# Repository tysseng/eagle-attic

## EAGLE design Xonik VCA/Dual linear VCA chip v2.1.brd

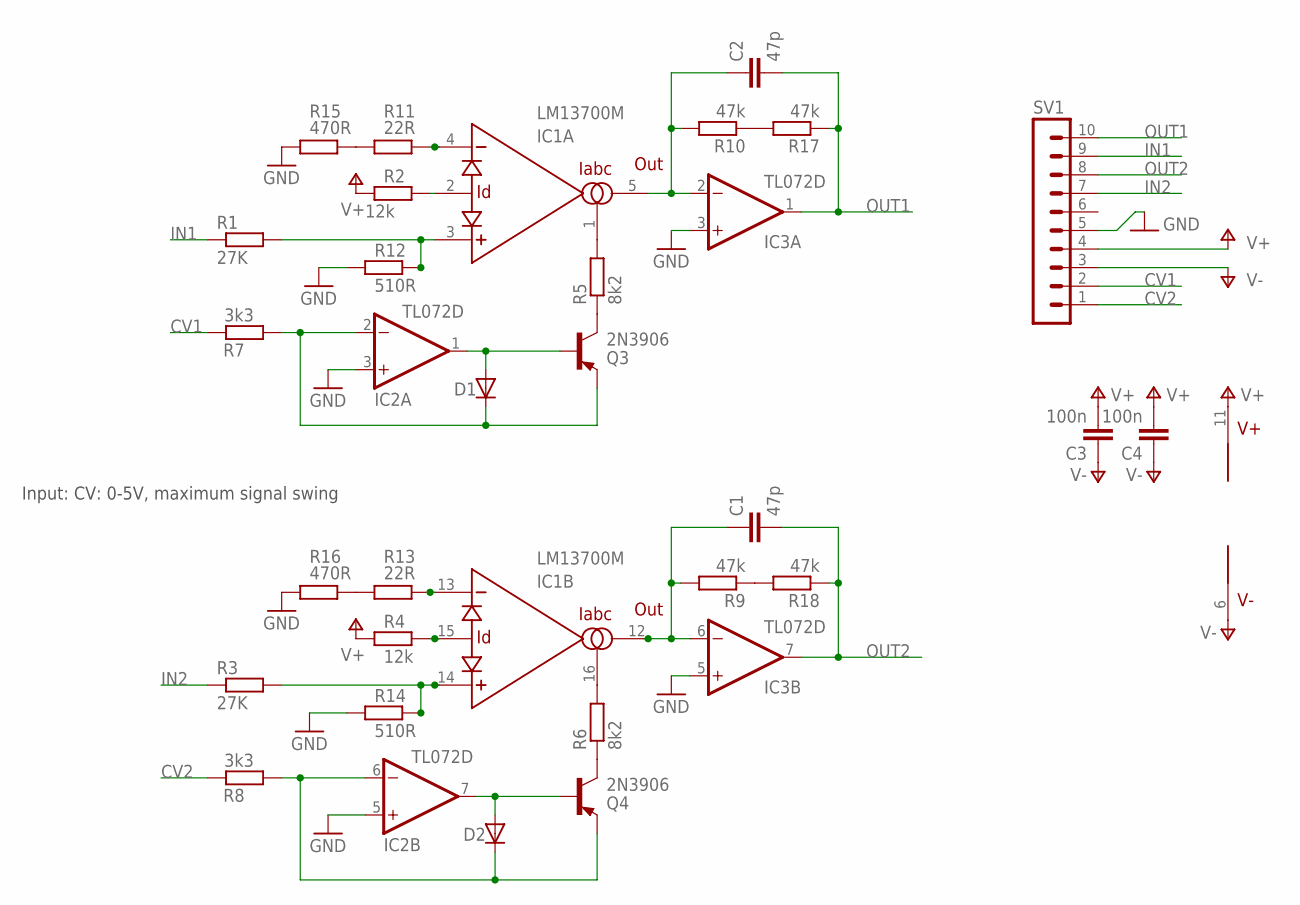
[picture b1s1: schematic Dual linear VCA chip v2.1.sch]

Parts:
C1, C2: 47p; C0805
C3, C4: 100n; C0805
D1, D2: DIODE-SOD80C; SOD80C
IC1: LM13700M; SO16
IC2, IC3: TL072D; SO08
Q3, Q4: 2N3906; TO92
R1, R3: 27K; R0805
R2, R4: 12k; R0805
R5, R6: 8k2; R0805
R7, R8: 3k3; R0805
R9, R10, R17, R18: 47k; R0805
R11, R13: 22R; R0805
R12, R14: 510R; R0805
R15, R16: 470R; R0805
SV1: MA10-1

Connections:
CV1: R7.2, SV1.2
CV2: R8.2, SV1.1
GND: IC2.3 (+IN), IC2.5 (+IN), IC3.3 (+IN), IC3.5 (+IN), R12.1, R14.1, R15.1, R16.1, SV1.5
IN1: R1.1, SV1.9
IN2: R3.1, SV1.7
unnamed: Q3.1 (C), R5.1
unnamed: Q4.1 (C), R6.1
unnamed: D1.C, IC2.2 (-IN), Q3.3 (E), R7.1
unnamed: IC1.1 (IABC), R5.2
unnamed: R11.1, R15.2
unnamed: IC1.2 (ID), R2.2
unnamed: R13.1, R16.2
unnamed: D2.A, IC2.7 (OUT), Q4.2 (B)
unnamed: C2.1, IC1.5 (OUT), IC3.2 (-IN), R10.2
unnamed: D1.A, IC2.1 (OUT), Q3.2 (B)
unnamed: D2.C, IC2.6 (-IN), Q4.3 (E), R8.1
unnamed: R10.1, R17.2
unnamed: IC1.16 (IABC), R6.2
unnamed: R9.1, R18.2
unnamed: IC1.15 (ID), R4.2
unnamed: C1.1, IC1.12 (OUT), IC3.6 (-IN), R9.2
OUT1: C2.2, IC3.1 (OUT), R17.1, SV1.10
OUT2: C1.2, IC3.7 (OUT), R18.1, SV1.8
TRIM1+: IC1.3 (+IN), R1.2, R12.2
TRIM1-: IC1.4 (-IN), R11.2
TRIM2+: IC1.14 (+IN), R3.2, R14.2
TRIM2-: IC1.13 (-IN), R13.2
V+: C3.2, C4.2, IC1.11 (V+), IC2.8 (V+), IC3.8 (V+), R2.1, R4.1, SV1.4
V-: C3.1, C4.1, IC1.6 (V-), IC2.4 (V-), IC3.4 (V-), SV1.3

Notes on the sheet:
Input: CV: 0-5V, maximum signal swing

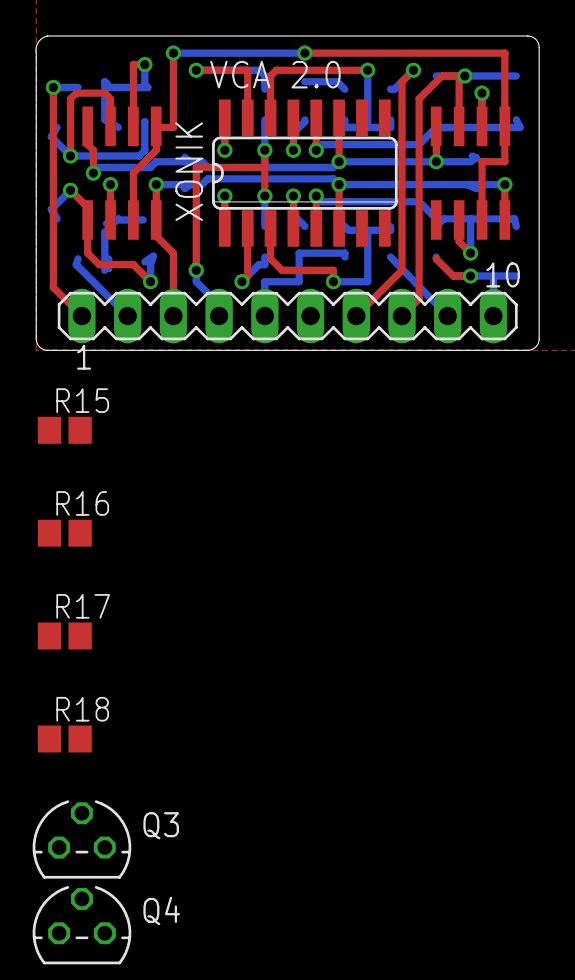
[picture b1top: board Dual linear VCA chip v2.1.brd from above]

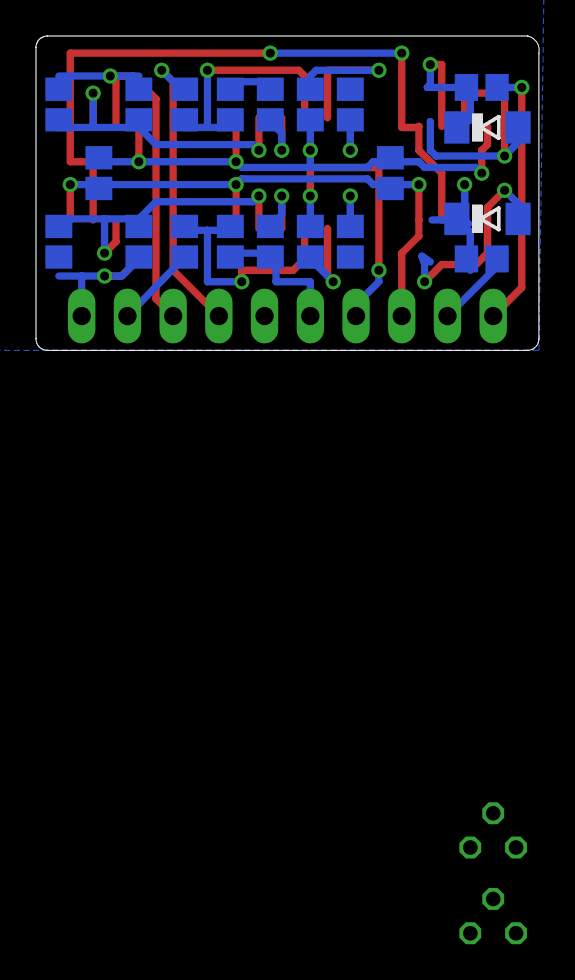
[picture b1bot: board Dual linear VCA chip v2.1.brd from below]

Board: 2 copper layers, 28.0 x 17.5 mm, 30 parts (20 on the bottom side), 29 nets.

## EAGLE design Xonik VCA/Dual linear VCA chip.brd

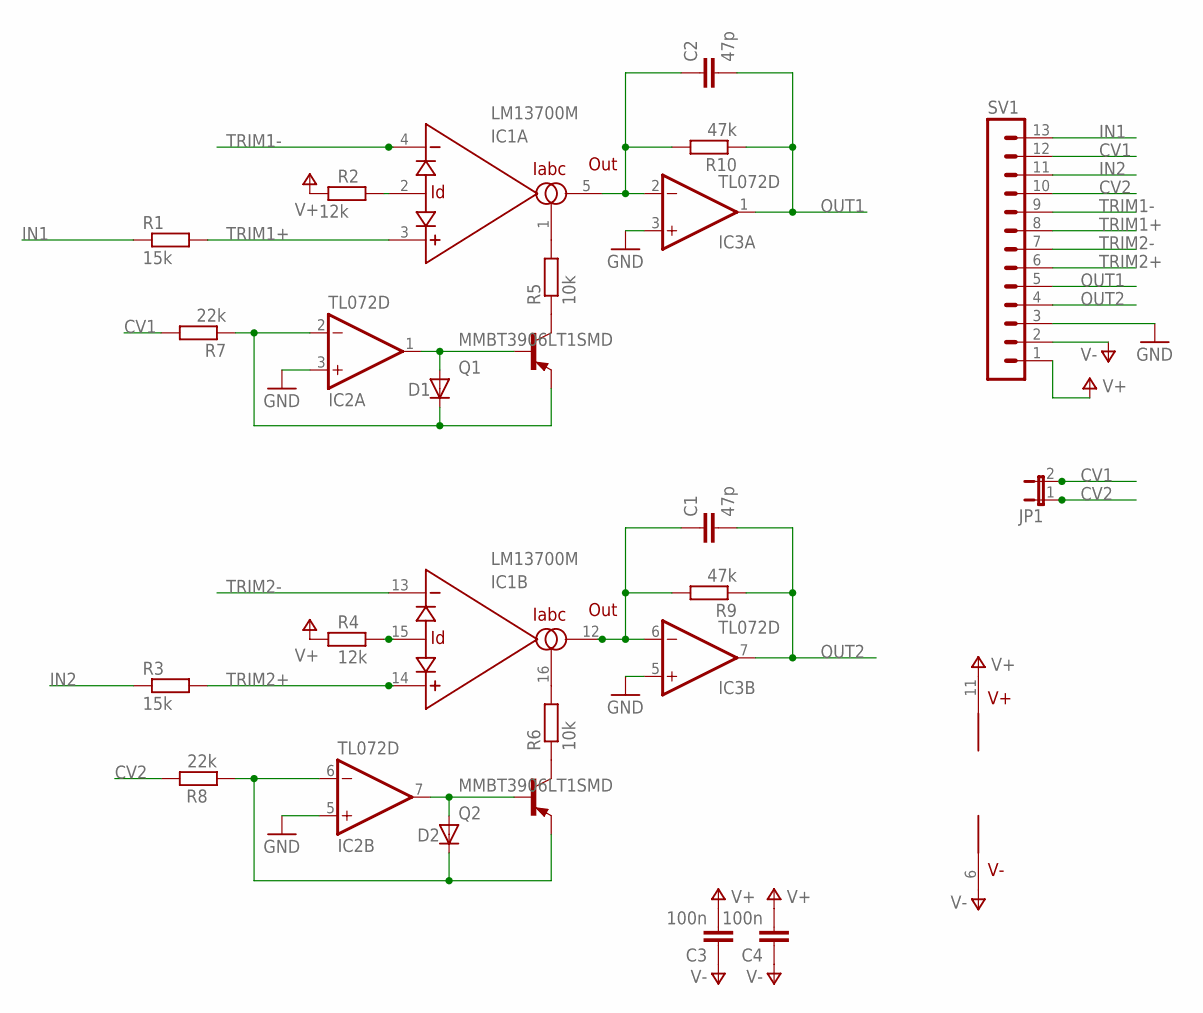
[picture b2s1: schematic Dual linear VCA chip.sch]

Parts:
C1, C2: 47p; C0805
C3, C4: 100n; C0805
D1, D2: DIODE-SOD80C; SOD80C
IC1: LM13700M; SO16
IC2, IC3: TL072D; SO08
JP1: JP1E; JP1
Q1, Q2: MMBT3906LT1SMD; SOT23-BEC
R1, R3: 15k; R0805
R2, R4: 12k; R0805
R5, R6: 10k; R0805
R7, R8: 22k; R0805
R9, R10: 47k; R0805
SV1: MA13-1

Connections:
CV1: JP1.2, R7.2, SV1.12
CV2: JP1.1, R8.2, SV1.10
GND: IC2.3 (+IN), IC2.5 (+IN), IC3.3 (+IN), IC3.5 (+IN), SV1.3
IN1: R1.1, SV1.13
IN2: R3.1, SV1.11
unnamed: Q1.C, R5.1
unnamed: Q2.C, R6.1
unnamed: D1.C, IC2.2 (-IN), Q1.E, R7.1
unnamed: IC1.1 (IABC), R5.2
unnamed: IC1.2 (ID), R2.2
unnamed: D2.A, IC2.7 (OUT), Q2.B
unnamed: C2.1, IC1.5 (OUT), IC3.2 (-IN), R10.2
unnamed: D1.A, IC2.1 (OUT), Q1.B
unnamed: D2.C, IC2.6 (-IN), Q2.E, R8.1
unnamed: IC1.16 (IABC), R6.2
unnamed: IC1.15 (ID), R4.2
unnamed: C1.1, IC1.12 (OUT), IC3.6 (-IN), R9.2
OUT1: C2.2, IC3.1 (OUT), R10.1, SV1.4
OUT2: C1.2, IC3.7 (OUT), R9.1, SV1.5
TRIM1+: IC1.3 (+IN), R1.2, SV1.8
TRIM1-: IC1.4 (-IN), SV1.9
TRIM2+: IC1.14 (+IN), R3.2, SV1.6
TRIM2-: IC1.13 (-IN), SV1.7
V+: C3.2, C4.2, IC1.11 (V+), IC2.8 (V+), IC3.8 (V+), R2.1, R4.1, SV1.1
V-: C3.1, C4.1, IC1.6 (V-), IC2.4 (V-), IC3.4 (V-), SV1.2

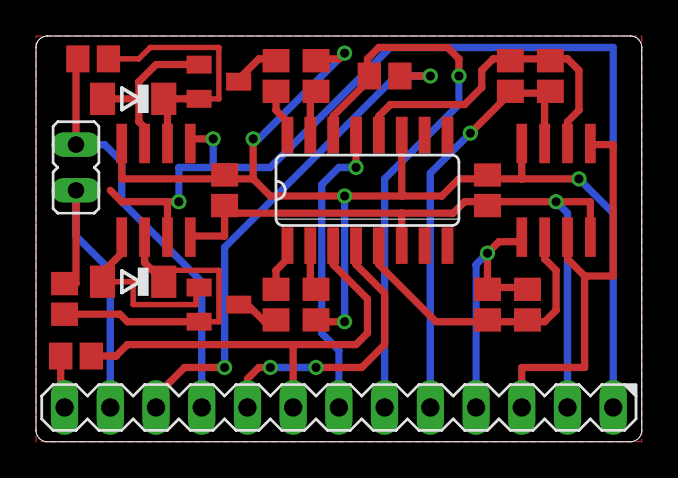
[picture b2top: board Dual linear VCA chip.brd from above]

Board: 2 copper layers, 33.7 x 22.5 mm, 23 parts (0 on the bottom side), 25 nets.

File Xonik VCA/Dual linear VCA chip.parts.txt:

Partlist

Exported from Dual linear VCA chip.sch at 25.02.2014 19:18:17

EAGLE Version 6.4.0 Copyright (c) 1988-2013 CadSoft

Assembly variant: 

Part     Value          Device         Package   Library        Sheet

C1       47p            C-EUC0805      C0805     resistor       1
C2       47p            C-EUC0805      C0805     resistor       1
C3       100n           C-EUC0805      C0805     resistor       1
C4       100n           C-EUC0805      C0805     resistor       1
D1                      DIODE-SOD80C   SOD80C    diode          1
D2                      DIODE-SOD80C   SOD80C    diode          1
IC1      LM13700M       LM13700M       SO16      synthdiy       1
IC2      TL072D         TL072D         SO08      linear         1
IC3      TL072D         TL072D         SO08      linear         1
JP1                     JP1E           JP1       jumper         1
Q1       MMBT3906LT1SMD MMBT3906LT1SMD SOT23-BEC transistor-pnp 1
Q2       MMBT3906LT1SMD MMBT3906LT1SMD SOT23-BEC transistor-pnp 1
R1       15k            R-EU_R0805     R0805     resistor       1
R2       12k            R-EU_R0805     R0805     resistor       1
R3       15k            R-EU_R0805     R0805     resistor       1
R4       12k            R-EU_R0805     R0805     resistor       1
R5       10k            R-EU_R0805     R0805     resistor       1
R6       10k            R-EU_R0805     R0805     resistor       1
R7       22k            R-EU_R0805     R0805     resistor       1
R8       22k            R-EU_R0805     R0805     resistor       1
R9       47k            R-EU_R0805     R0805     resistor       1
R10      47k            R-EU_R0805     R0805     resistor       1
SV1                     MA13-1         MA13-1    con-lstb       1

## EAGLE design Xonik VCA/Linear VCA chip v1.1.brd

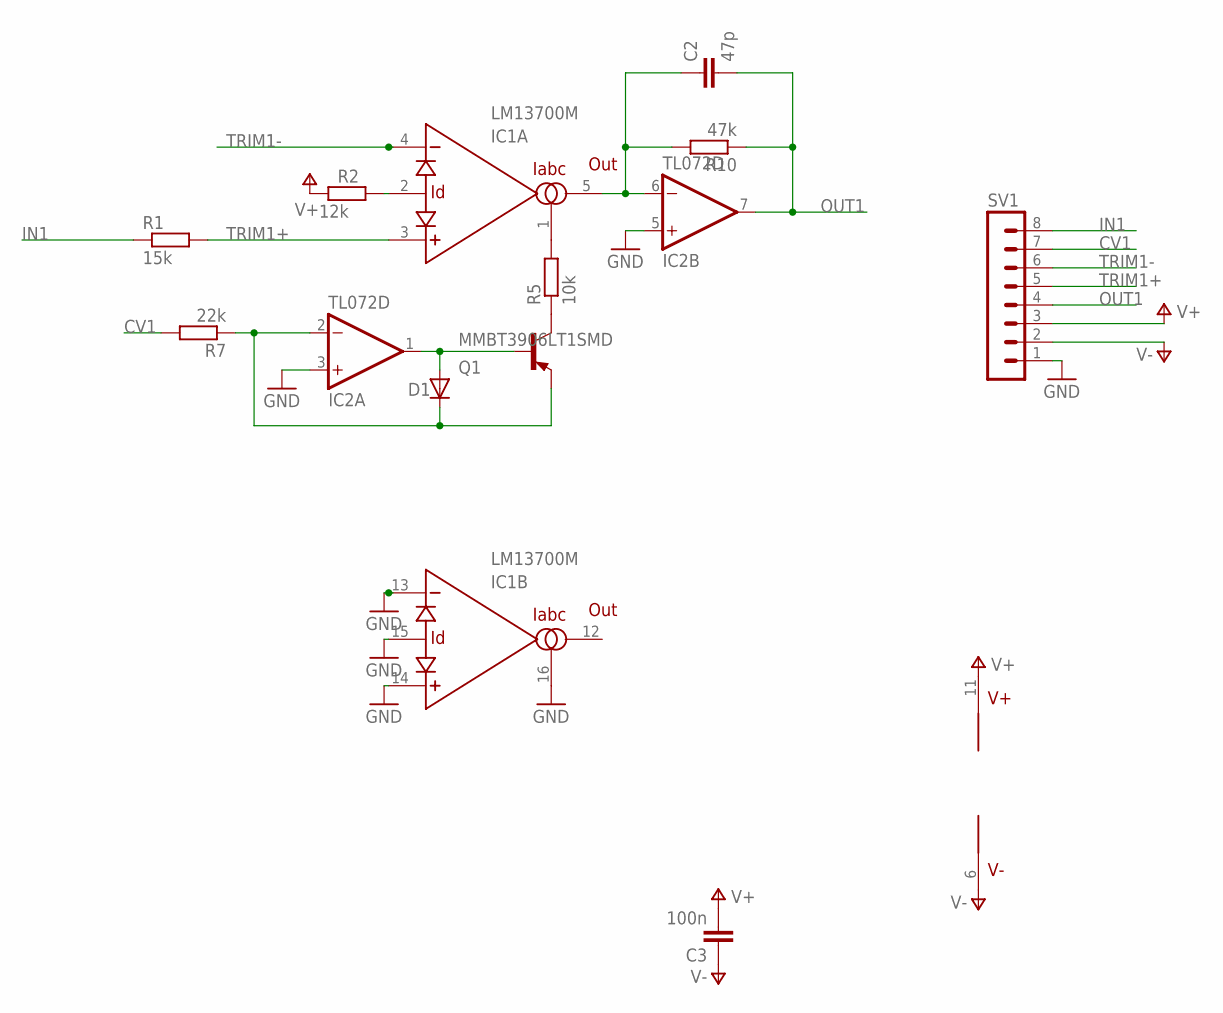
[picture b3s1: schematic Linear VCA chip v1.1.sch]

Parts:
C2: 47p; C0805
C3: 100n; C0805
D1: DIODE-SOD80C; SOD80C
IC1: LM13700M; SO16
IC2: TL072D; SO08
Q1: MMBT3906LT1SMD; SOT23-BEC
R1: 15k; R0805
R2: 12k; R0805
R5: 10k; R0805
R7: 22k; R0805
R10: 47k; R0805
SV1: MA08-1

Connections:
CV1: R7.2, SV1.7
GND: IC1.13 (-IN), IC1.14 (+IN), IC1.15 (ID), IC1.16 (IABC), IC2.3 (+IN), IC2.5 (+IN), SV1.1
IN1: R1.1, SV1.8
unnamed: Q1.C, R5.1
unnamed: D1.C, IC2.2 (-IN), Q1.E, R7.1
unnamed: IC1.1 (IABC), R5.2
unnamed: IC1.2 (ID), R2.2
unnamed: C2.1, IC1.5 (OUT), IC2.6 (-IN), R10.2
unnamed: D1.A, IC2.1 (OUT), Q1.B
OUT1: C2.2, IC2.7 (OUT), R10.1, SV1.4
TRIM1+: IC1.3 (+IN), R1.2, SV1.5
TRIM1-: IC1.4 (-IN), SV1.6
V+: C3.2, IC1.11 (V+), IC2.8 (V+), R2.1, SV1.3
V-: C3.1, IC1.6 (V-), IC2.4 (V-), SV1.2

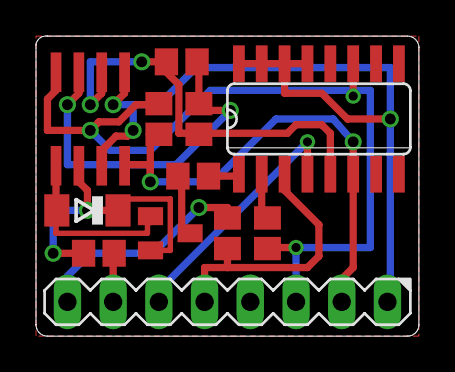
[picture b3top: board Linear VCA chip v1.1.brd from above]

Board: 2 copper layers, 21.3 x 16.7 mm, 12 parts (0 on the bottom side), 14 nets.
